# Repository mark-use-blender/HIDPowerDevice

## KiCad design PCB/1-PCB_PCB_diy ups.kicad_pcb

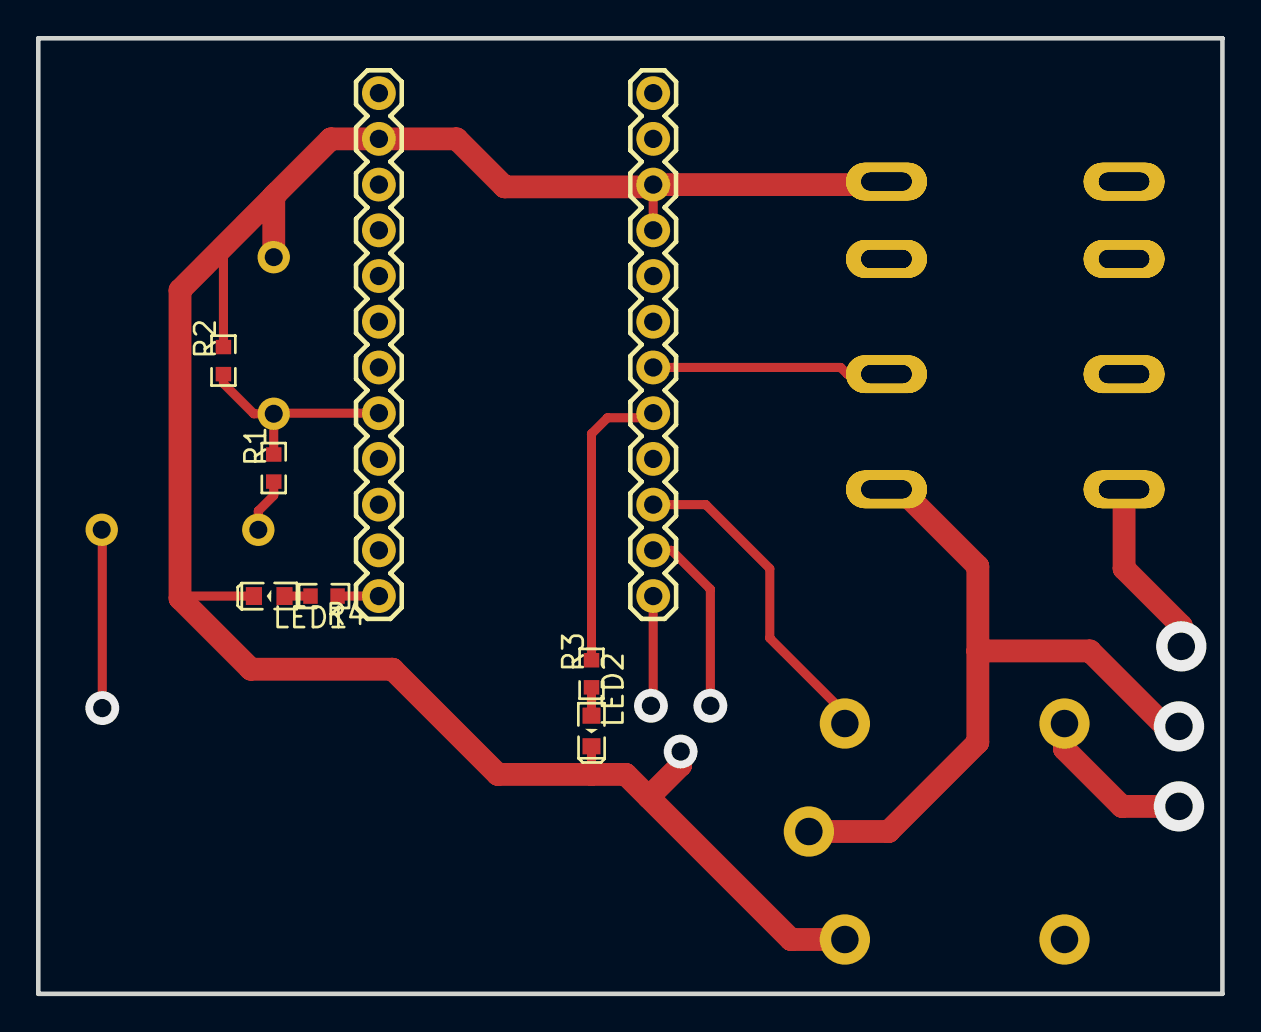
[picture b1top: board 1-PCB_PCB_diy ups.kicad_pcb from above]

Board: 2 copper layers, 65.8 x 53.1 mm, 11 parts (0 on the bottom side), 10 nets.

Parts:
D1: 5.1v; DO-41_BD2.4-L4.7-P8.70-D0.9-RD
D2: 10v; DO-41_BD2.4-L4.7-P8.70-D0.9-RD
LED1, LED2: LED-0603_R; LED0603_RED
P1: 10; PRO MICRO - 5V
R1: 1k; R0603
R2: 100k; R0603
R3, R4: 220; R0603
RLY1: SRD-05VDC-SL-C; RELAY-TH_SRD-XXVDC-XL-C
U1: MY2P_HH52P

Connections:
D1_1: D1.1, P1.20, R1.2, R2.1
D2_2: D2.2, R1.1
GND: D1.2, LED1.2, LED2.2, P1.9, P1.10, P1.14, R2.2, RLY1.4, U1.5
L: RLY1.5, U1.1
LED1_1: LED1.1, R4.2
LED2_1: LED2.1, R3.1
R3_2: P1.5, R3.2
R4_1: P1.24, R4.1
RLY1_1: P1.3, RLY1.1
U1_3: P1.6, U1.3

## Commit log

2025-12-29 empty
2025-12-29 modified to suit personal use
2025-12-29 PCB_file
2025-12-30 fix serial bug
2025-12-30 cleanup
2026-01-05 provide script to interface with truenas
